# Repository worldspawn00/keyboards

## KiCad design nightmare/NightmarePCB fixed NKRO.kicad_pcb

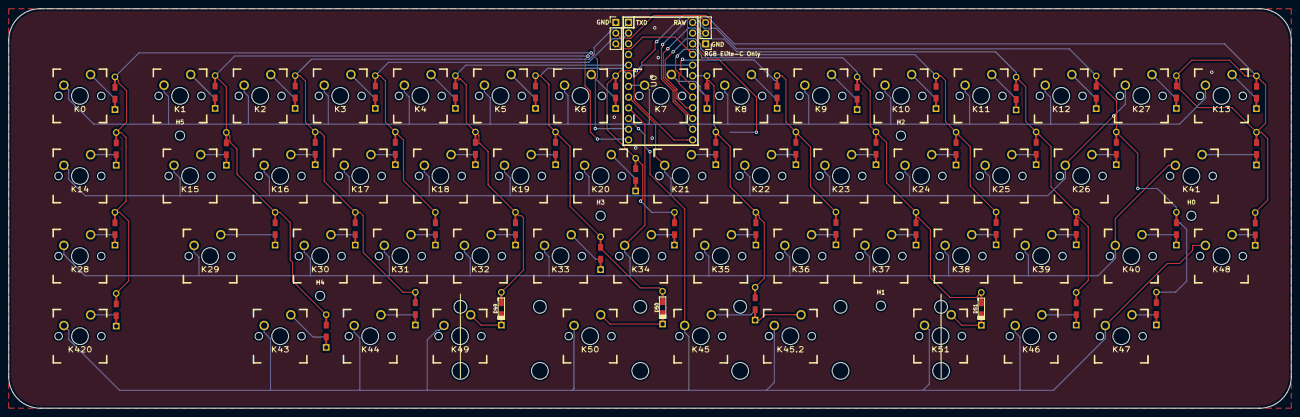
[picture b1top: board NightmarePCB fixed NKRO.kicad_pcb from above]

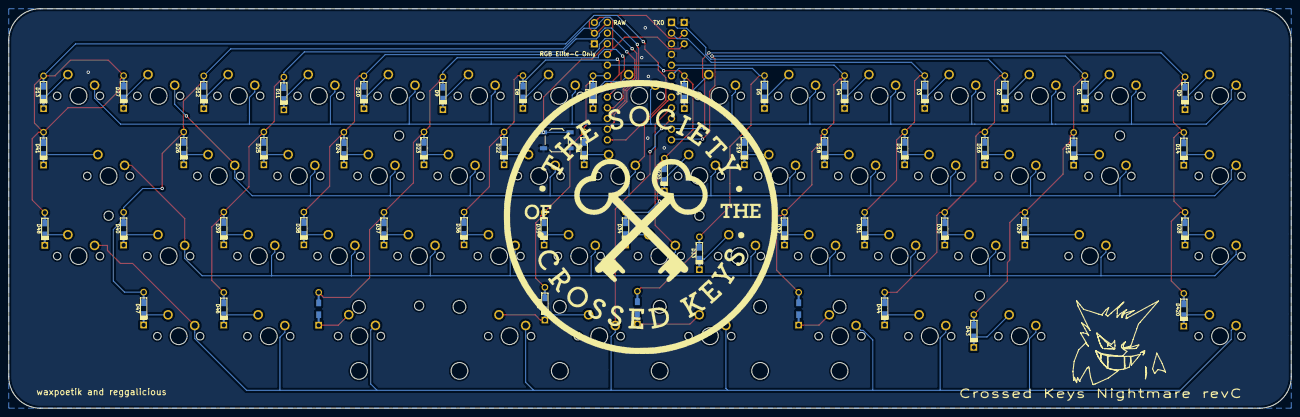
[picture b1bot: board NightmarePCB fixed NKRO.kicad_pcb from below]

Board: 2 copper layers, 305.0 x 95.0 mm, 115 parts (50 on the bottom side), 36 nets.

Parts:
 : PinHeader_1x03_P2.54mm_Vertical
 #2: PinHeader_1x03_P2.54mm_Vertical
 #3: SW_SPST_TL3342
D0, D1, D2, D3, D4, D5, D6, D7, D8, D9, D10, D11, D12, D13, D14, D15, D16, D17, D18, D19, D20, D21, D22, D23, D24, D25, D26, D27, D28, D29, D30, D31, D32, D33, D34, D35, D36, D37, D38, D39, D40, D41, D43, D44, D45, D46, D47, D48, D49, D50, D51, D420: 1N4148; Diode-dual
H0, H1, H2, H3, H4, H5: MountingHole_2.2mm_M2
K0, K1, K2, K3, K4, K5, K6, K7, K8, K9, K10, K11, K12, K13, K14, K16, K17, K18, K19, K20, K21, K22, K23, K24, K25, K26, K27, K28, K30, K31, K32, K33, K34, K35, K36, K37, K38, K39, K43, K47, K48, K49, K51, K420: KEYSW; MX_PCB_100H
K15, K40, K44, K46: KEYSW; MX_PCB_125H
K29, K41: KEYSW; MX_PCB_175H
K45: KEYSW; MX_PCB_700H
K45.2: KEYSW; MX_PCB_275H
K50: KEYSW; MX_PCB_225H
U0: ProMicro; ARDUINO_PRO_MICRO

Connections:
/col0: D0.1, D0.2, D14.1, D14.2, D28.1, D28.2, D420.2, K0.1, K14.1, K28.1, U0.11
/col1: D1.1, D1.2, D15.1, D15.2, D29.1, D29.2, D43.2, K1.1, K15.1, K29.1, U0.12
/col2: D2.1, D2.2, D16.1, D16.2, D30.1, D30.2, D44.2, K2.1, K16.1, K30.1, U0.1
/col3: D3.1, D3.2, D17.1, D17.2, D31.2, K3.1, K17.1, U0.2
/col4: D4.1, D4.2, D18.1, D18.2, D32.1, D32.2, D49.2, K4.1, K18.1, K32.1, U0.5
/col5: D5.1, D5.2, D19.1, D19.2, D33.1, D33.2, D50.2, K5.1, K19.1, K33.1, U0.6
/col6: D6.1, D6.2, D20.1, D20.2, D34.2, K6.1, K20.1, U0.20
/col7: D7.1, D7.2, D21.1, D21.2, D35.1, D35.2, D45.2, K7.1, K21.1, K35.1, U0.19
/col8: D8.1, D8.2, D22.1, D22.2, D36.2, K8.1, K22.1, U0.18
/col9: D9.1, D9.2, D23.1, D23.2, D37.1, D37.2, D51.2, K9.1, K23.1, K37.1, U0.17
/col10: D10.1, D10.2, D24.1, D24.2, D38.2, K10.1, K24.1, U0.16
/col11: D11.1, D11.2, D25.1, D25.2, D39.1, D39.2, D46.2, K11.1, K25.1, K39.1, U0.15
/col12: D12.1, D12.2, D26.1, D26.2, D40.1, D40.2, D47.2, K12.1, K26.1, K40.1, U0.14
/col13: D13.1, D13.2, D27.1, D27.2, D41.1, D41.2, D48.2, K13.1, K27.1, K41.1, U0.13
/row0: K0.2, K1.2, K2.2, K3.2, K4.2, K5.2, K6.2, K7.2, K8.2, K9.2, K10.2, K11.2, K12.2, K13.2, U0.7
/row1: K14.2, K15.2, K16.2, K17.2, K18.2, K19.2, K20.2, K21.2, K22.2, K23.2, K24.2, K25.2, K26.2, K27.2, U0.8
/row2: K28.2, K29.2, K30.2, K31.2, K32.2, K33.2, K34.2, K35.2, K36.2, K37.2, K38.2, K39.2, K40.2, K41.2, U0.9
/row3: K43.2, K44.2, K45.2, K45.2.2, K46.2, K47.2, K48.2, K49.2, K50.2, K51.2, K420.2, U0.10
GND: .1, #2.1, #3.2, U0.3, U0.4, U0.23
unnamed: D31.1, K31.1
unnamed: D34.1, K34.1
unnamed: D36.1, K36.1
unnamed: D38.1, K38.1
unnamed: D43.1, K43.1
unnamed: D44.1, K44.1
unnamed: D45.1, K45.1, K45.2.1
unnamed: D46.1, K46.1
unnamed: D47.1, K47.1
unnamed: D48.1, K48.1
unnamed: D49.1, K49.1
unnamed: D50.1, K50.1
unnamed: D51.1, K51.1
unnamed: D420.1, K420.1
unnamed: #3.1, U0.22
unnamed: .2, #2.2, U0.24
VCC: .3, #2.3, U0.21

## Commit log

2020-06-05 creating compact PCB and QMK firmware
2020-06-05 adding RGB+NKRO original PCB to repo
